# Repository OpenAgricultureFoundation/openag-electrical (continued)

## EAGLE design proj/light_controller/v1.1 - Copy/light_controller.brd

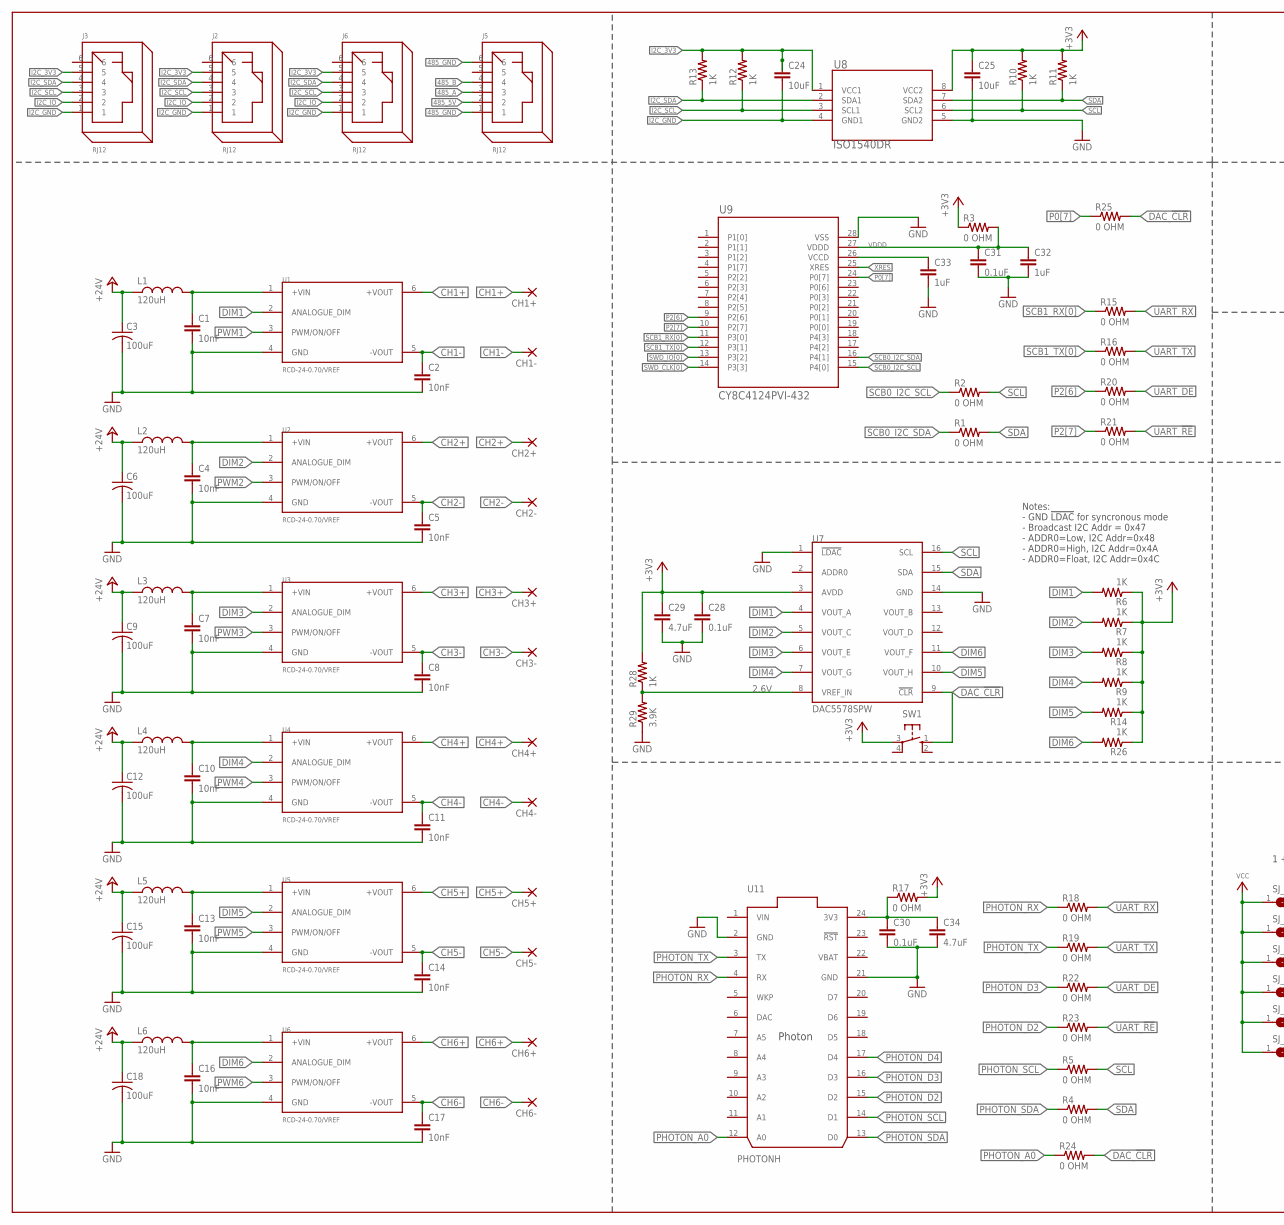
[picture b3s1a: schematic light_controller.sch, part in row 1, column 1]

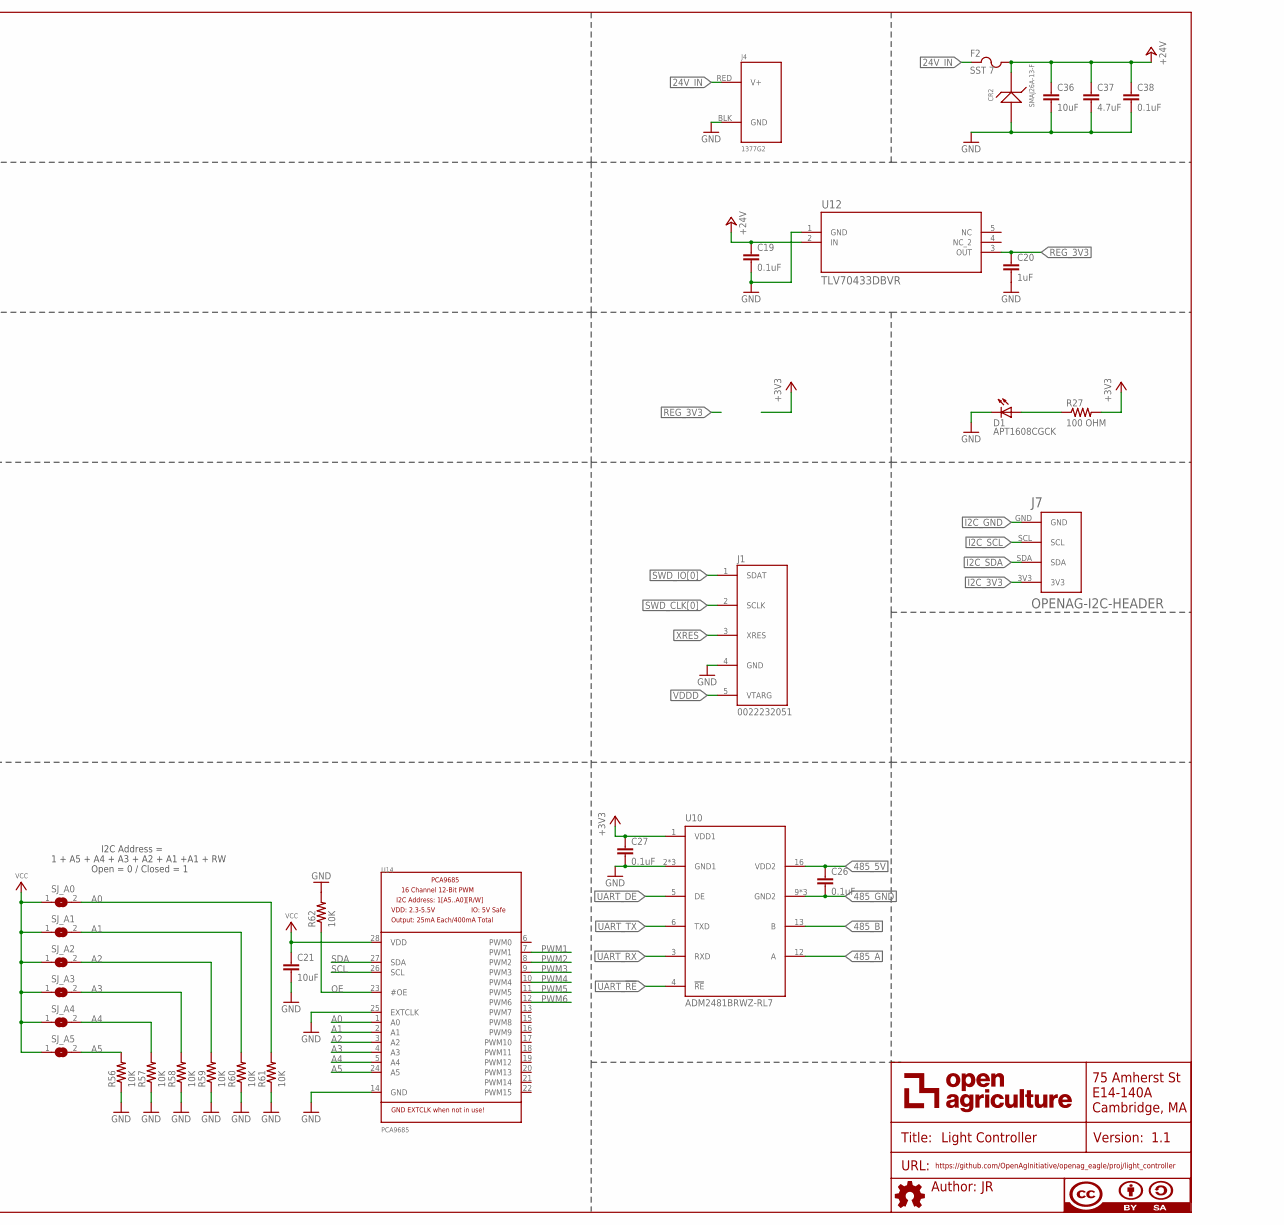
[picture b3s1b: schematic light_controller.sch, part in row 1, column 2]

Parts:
C1, C2, C4, C5, C7, C8, C10, C11, C13, C14, C16, C17: 10nF; C0603
C3, C6, C9, C12, C15, C18: 100uF; EEE-1HA101UP
C19, C26, C27, C28, C30, C31, C38: 0.1uF; C0603
C20, C32, C33: 1uF; C0603
C21, C24, C25, C36: 10uF; C0805
C29, C34, C37: 4.7uF; C0805
CH1+, CH1-, CH2+, CH2-, CH3+, CH3-, CH4+, CH4-, CH5+, CH5-, CH6+, CH6-: 3,17/1,3
CR2: SMAJ26A-13-F; SMA
D1: APT1608CGCK; CHIPLED_0603
F2: SST 7; SS
FRAME1: DOCFIELD
J1: 0022232051; 22-23-2051
J2, J3, J5, J6: RJ12
J4: 1377G2
J7: OPENAG-I2C-HEADER
L1, L2, L3, L4, L5, L6: 120uH; 74404064121
R1, R2, R3, R4, R5, R15, R16, R17, R18, R19, R20, R21, R22, R23, R24, R25: 0 OHM; RC0603N
R6, R7, R8, R9, R10, R11, R12, R13, R14, R26, R28: 1K; RC0603N
R27: 100 OHM; RC0603N
R29: 3.9K; RC0603N
R56, R57, R58, R59, R60, R61, R62: 10K; RC0603N
SJ_A0, SJ_A1, SJ_A2, SJ_A3, SJ_A4, SJ_A5: SOLDERJUMPERREFLOW_NOPASTE; SOLDERJUMPER_REFLOW_NOPASTE
SW1: BF3-1020; B3F-10XX
U1, U2, U3, U4, U5, U6: RCD-24-0.70/VREF; RCD-24-PINNED
U7: DAC5578SPW; TSSOP16
U8: ISO1540DR; D8
U9: CY8C4124PVI-432; SSOP-28
U10: ADM2481BRWZ-RL7; SOIC16LWB
U11: PHOTONH; PHOTON
U12: TLV70433DBVR; DBV5-M
U14: PCA9685; TSSOP28

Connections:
2.6V: R28.1, R29.2, U7.8 (VREF_IN)
24V_IN: F2.1, J4.RED (V+)
485_5V: C26.1, J5.2, U10.16 (VDD2)
485_A: J5.3, U10.12 (A)
485_B: J5.4, U10.13 (B)
485_GND: C26.2, J5.1, J5.6, U10.9 (GND2), U10.10 (GND2), U10.15 (GND2)
+3V3: C25.1, C27.1, C28.1, C29.1, R3.1, R6.1, R7.1, R8.1, R9.1, R10.2, R11.2, R14.1, R17.2, R26.1, R27.2, R28.2, SW1.3, U7.3 (AVDD), U8.8 (VCC2), U10.1 (VDD1)
+24V: C3.+ (1(+)), C6.+ (1(+)), C9.+ (1(+)), C12.+ (1(+)), C15.+ (1(+)), C18.+ (1(+)), C19.1, C36.1, C37.1, C38.1, CR2.1, F2.2, L1.1, L2.1, L3.1, L4.1, L5.1, L6.1, U12.2 (IN)
A0: R61.2, SJ_A0.2, U14.1 (A0)
A1: R60.2, SJ_A1.2, U14.2 (A1)
A2: R59.2, SJ_A2.2, U14.3 (A2)
A3: R58.2, SJ_A3.2, U14.4 (A3)
A4: R57.2, SJ_A4.2, U14.5 (A4)
A5: R56.2, SJ_A5.2, U14.24 (A5)
CH1+: CH1+.1, U1.6 (+VOUT)
CH1-: C2.1, CH1-.1, U1.5 (-VOUT)
CH2+: CH2+.1, U2.6 (+VOUT)
CH2-: C5.1, CH2-.1, U2.5 (-VOUT)
CH3+: CH3+.1, U3.6 (+VOUT)
CH3-: C8.1, CH3-.1, U3.5 (-VOUT)
CH4+: CH4+.1, U4.6 (+VOUT)
CH4-: C11.1, CH4-.1, U4.5 (-VOUT)
CH5+: CH5+.1, U5.6 (+VOUT)
CH5-: C14.1, CH5-.1, U5.5 (-VOUT)
CH6+: CH6+.1, U6.6 (+VOUT)
CH6-: C17.1, CH6-.1, U6.5 (-VOUT)
DAC_!CLR!: R24.2, R25.2, SW1.1 (S), U7.9 (!CLR!)
DIM1: R6.2, U1.2 (ANALOGUE_DIM), U7.4 (VOUT_A)
DIM2: R7.2, U2.2 (ANALOGUE_DIM), U7.5 (VOUT_C)
DIM3: R8.2, U3.2 (ANALOGUE_DIM), U7.6 (VOUT_E)
DIM4: R9.2, U4.2 (ANALOGUE_DIM), U7.7 (VOUT_G)
DIM5: R14.2, U5.2 (ANALOGUE_DIM), U7.10 (VOUT_H)
DIM6: R26.2, U6.2 (ANALOGUE_DIM), U7.11 (VOUT_F)
GND: C1.2, C2.2, C3.- (2(-)), C4.2, C5.2, C6.- (2(-)), C7.2, C8.2, C9.- (2(-)), C10.2, C11.2, C12.- (2(-)), C13.2, C14.2, C15.- (2(-)), C16.2, C17.2, C18.- (2(-)), C19.2, C20.2, C21.2, C25.2, C27.2, C28.2, C29.2, C30.2, C31.2, C32.2, C33.2, C34.2, C36.2, C37.2, C38.2, CR2.2, D1.C, J1.4 (GND), J4.BLK (GND), R29.1, R56.1, R57.1, R58.1, R59.1, R60.1, R61.1, R62.2, U1.4 (GND), U2.4 (GND), U3.4 (GND), U4.4 (GND), U5.4 (GND), U6.4 (GND), U7.1 (!LDAC!), U7.14 (GND), U8.5 (GND2), U9.28 (VSS), U10.2 (GND1), U10.7 (GND1), U10.8 (GND1), U11.2 (GND), U11.21 (GND), U12.1 (GND), U14.14 (GND), U14.25 (EXTCLK)
I2C_3V3: C24.1, J2.5, J3.5, J6.5, J7.3V3, R12.2, R13.2, U8.1 (VCC1)
I2C_GND: C24.2, J2.1, J3.1, J6.1, J7.GND, U8.4 (GND1)
I2C_IO: J2.2, J3.2, J6.2
I2C_SCL: J2.3, J3.3, J6.3, J7.SCL, R12.1, U8.3 (SCL1)
I2C_SDA: J2.4, J3.4, J6.4, J7.SDA, R13.1, U8.2 (SDA1)
unnamed: C1.1, L1.2, U1.1 (+VIN)
unnamed: C4.1, L2.2, U2.1 (+VIN)
unnamed: D1.A, R27.1
unnamed: C7.1, L3.2, U3.1 (+VIN)
unnamed: C10.1, L4.2, U4.1 (+VIN)
unnamed: C13.1, L5.2, U5.1 (+VIN)
unnamed: C16.1, L6.2, U6.1 (+VIN)
unnamed: C30.1, C34.1, R17.1, U11.24 (3V3)
unnamed: C33.1, U9.26 (VCCD)
OE: R62.1, U14.23 (#OE)
P0[7]: R25.1, U9.24 (P0[7])
P2[6]: R20.1, U9.9 (P2[6])
P2[7]: R21.1, U9.10 (P2[7])
PHOTON_A0: R24.1, U11.12 (A0)
PHOTON_D2: R23.1, U11.15 (D2)
PHOTON_D3: R22.1, U11.16 (D3)
PHOTON_D4: U11.17 (D4)
PHOTON_RX: R18.1, U11.4 (RX)
PHOTON_SCL: R5.1, U11.14 (D1)
PHOTON_SDA: R4.1, U11.13 (D0)
PHOTON_TX: R19.1, U11.3 (TX)
PWM1: U1.3 (PWM/ON/OFF), U14.7 (PWM1)
PWM2: U2.3 (PWM/ON/OFF), U14.8 (PWM2)
PWM3: U3.3 (PWM/ON/OFF), U14.9 (PWM3)
PWM4: U4.3 (PWM/ON/OFF), U14.10 (PWM4)
PWM5: U5.3 (PWM/ON/OFF), U14.11 (PWM5)
PWM6: U6.3 (PWM/ON/OFF), U14.12 (PWM6)
REG_3V3: C20.1, U12.3 (OUT)
SCB0_I2C_SCL: R2.1, U9.15 (P4[0])
SCB0_I2C_SDA: R1.1, U9.16 (P4[1])
SCB1_RX[0]: R15.1, U9.11 (P3[0])
SCB1_TX[0]: R16.1, U9.12 (P3[1])
SCL: R2.2, R5.2, R10.1, U7.16 (SCL), U8.6 (SCL2), U14.26 (SCL)
SDA: R1.2, R4.2, R11.1, U7.15 (SDA), U8.7 (SDA2), U14.27 (SDA)
SWD_CLK[0]: J1.2 (SCLK), U9.14 (P3[3])
SWD_IO[0]: J1.1 (SDAT), U9.13 (P3[2])
UART_!RE!: R21.2, R23.2, U10.4 (!RE!)
UART_DE: R20.2, R22.2, U10.5 (DE)
UART_RX: R15.2, R18.2, U10.3 (RXD)
UART_TX: R16.2, R19.2, U10.6 (TXD)
VBAT: U11.22 (VBAT)
VCC: C21.1, SJ_A0.1, SJ_A1.1, SJ_A2.1, SJ_A3.1, SJ_A4.1, SJ_A5.1, U14.28 (VDD)
VDDD: C31.1, C32.1, J1.5 (VTARG), R3.2, U9.27 (VDDD)
VIN: U11.1 (VIN)
XRES: J1.3 (XRES), U9.25 (XRES)

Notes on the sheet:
Notes: - GND !LDAC! for syncronous mode - Broadcast I2C Addr = 0x47 - ADDR0=Low, I2C Addr=0x48 - ADDR0=High, I2C Addr=0x4A - ADDR0=Float, I2C Addr=0x4C
1 + A5 + A4 + A3 + A2 + A1 +A1 + RW
I2C Address =
Open = 0 / Closed = 1

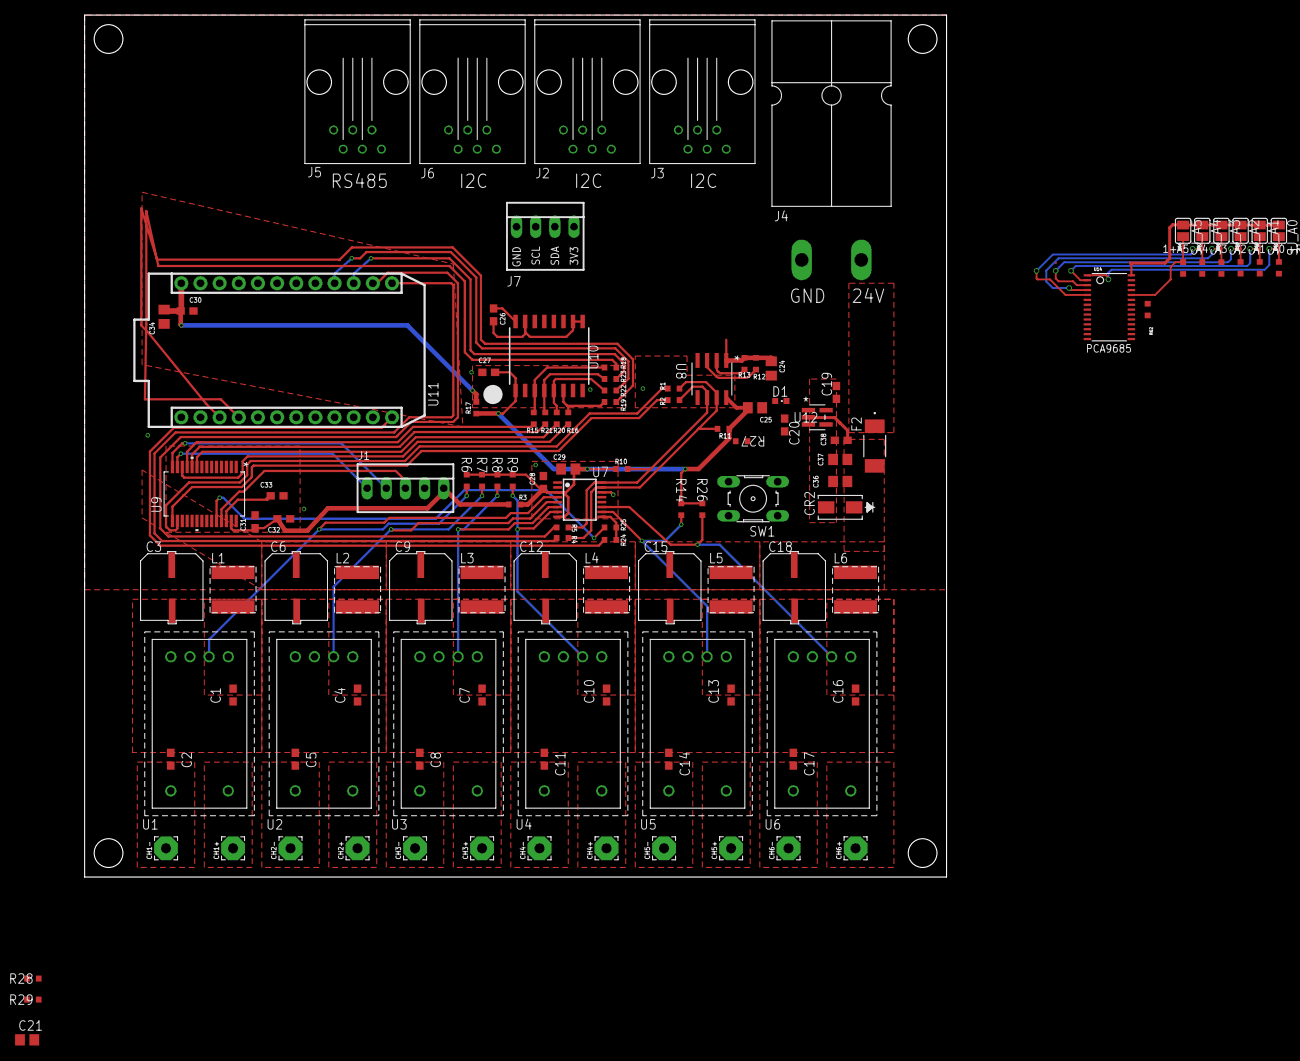
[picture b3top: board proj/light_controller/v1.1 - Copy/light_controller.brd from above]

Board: 2 copper layers, 114.3 x 114.3 mm, 120 parts (1 on the bottom side), 81 nets.

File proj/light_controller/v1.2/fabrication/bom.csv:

Qty,Value,Device,Package,Parts,Description,,
20,0 OHM,0OHM-RC0603JR-070RL,RC0603N,R1 / R2 / R3 / R4 / R5 / R15 / R16 / R17 / R18 / R19 / R20 / R21 / R22 / R23 / R24 / R25 / R30 / R31 / R32 / R33,Yageo - RC0603JR-070RL - RES SMD 0 OHM JUMPER 1/10W 0603,,
7,0.1uF,0.1UF-C0603C104K5RACTU,C0603,C19 / C26 / C27 / C28 / C30 / C31 / C38,Kemet - C0603C104K5RACTU - CAP CER 0.1UF 50V X7R 0603,,
1,0022232051,MINI-PROG3-5POS-MATING-CONNECTOR,22-23-2051,J1,Molex - 0022232051 - CONN HEADER 5POS .100 VERT TIN,,
1,100 OHM,100OHM-RC0603JR-07100RL,RC0603N,R27,Yageo - RC0603JR-07100RL - RES SMD 100 OHM 5% 1/10W 0603,,
6,100uF,100UF-EEE-1HA101UP,EEE-1HA101UP,C3 / C6 / C9 / C12 / C15 / C18,Panasonic - EEE-1HA101UP - ELECTROLYTIC CAP ALUM 100UF 20% 50V SMD,,
7,10K,10K-ERJ-3EKF1002V,RC0603N,R56 / R57 / R58 / R59 / R60 / R61 / R62,Panasonic - ERJ-3EKF1002V - RES SMD 10K OHM 1% 1/10W 0603,,
12,10nF,10NF-C0603C103K5RACTU,C0603,C1 / C2 / C4 / C5 / C7 / C8 / C10 / C11 / C13 / C14 / C16 / C17,KEMET - C0603C103K5RACTU - CAP CER 10000PF 50V X7R 0603,,
4,10uF,10UF-GMK212BBJ106KG-T,C0805,C21 / C24 / C25 / C36,Taiyo Yuden - GMK212BBJ106KG-T - CAP CER 10UF 35V X5R 0805,,
6,120uH,120UH-74404064121,74404064121,L1 / L2 / L3 / L4 / L5 / L6,Wurth Electronics - 74404064121 - FIXED IND 120UH 790MA 520 MOHM,,
1,1377G2,1377G21377G2,1377G2,J4,Anderson Powerpole - 1377G2 - RT. ANGLE 25A THRU-HOLE PCB CONTACT PAIR FOR 15/45 HOUSING,,
11,1K,1K-ERJ-PB3D1001V,RC0603N,R6 / R7 / R8 / R9 / R10 / R11 / R12 / R13 / R14 / R26 / R28,Panasonic - P20283CT-ND - RES SMD 1K OHM 0.5% 1/5W 0603,,
3,1uF,1UF-CL10A105KB8NNNC,C0603,C20 / C32 / C33,Samsung - CL10A105KB8NNNC - CAP CER 1UF 50V X5R 0603,,
1,3.9K,3.9K-RC0603JR-073K9L,RC0603N,R29,Yageo - RC0603JR-073K9L - RES SMD 3.9K OHM 5% 1/10W 0603,,
3,4.7uF,4.7UF-CL21A475KBQNNNE,C0805,C29 / C34 / C37,Samsung - CL21A475KBQNNNE - CAP CER 4.7UF 50V X5R 0805,,
4,A-2004-1-4-LP-N-R,A-2004-1-4-LP-N-R,RJ12,J2 / J3 / J5 / J6,Assmann WSW Components - A-2004-1-4-LP-N-R - RJ12 CONN MOD JACK 6P6C R/A UNSHLD,,
1,ADM2481BRWZ-RL7,ADM2481BRWZ-RL7,SOIC16LWB,U10,Analog Devices - ADM2481BRWZ-RL7 - DGTL ISO RS422/RS485 16SOIC,,
1,APT1608CGCK,APT1608CGCK,CHIPLED_0603,D1,Kingbright - APT1608CGCK - LED GREEN CLEAR 0603 SMD,,
1,BF3-1020,BF3-1020,B3F-10XX,SW1,Omron - BF3-1020 -SWITCH TACTILE SPST-NO 0.05A 24V,,
1,CY8C4124PVI-432,CY8C4124PVI-432,SSOP-28,U9,Cypress - CY8C4124PVI-432 - IC MCU 32BIT 16KB FLASH 28SSOP,,
1,DAC5578SPW,DAC5578SPW,TSSOP16,U7,Texas Instruments - DAC5578SPW,,
1,ISO1540DR,ISO1540DR,D8,U8,Texas Instruments - ISO1540DR - DGTL ISO 2.5KV 2CH I2C 8SOIC,,
1,OPENAG-I2C-HEADER,OPENAG-I2C-HEADER,OPENAG-I2C-HEADER,J7,Fits standard 100 mil header footprint,,
1,PCA9685,PCA9685PW/Q900 /118,TSSOP28,U14,NXP USA Inc. - PCA9685PW/Q900 /118 - IC LED DRVR LIN DIM 25MA 28TSSOP,,
1,PHOTONH,PHOTONHPHOTONH,PHOTON,U11,PARTICLE - PHOTONH - Tiny Wi-Fi dev board w/cloud backend,,
6,RCD-24-0.70/VREF,RCD-24-0.70/VREF,RCD-24-PINNED,U1 / U2 / U3 / U4 / U5 / U6,Recom Power - RCD-24-0.70/VREF - LED SUPPLY CC BUCK 2-35V 700MA,,
1,SMAJ26A-13-F,SMAJ26A-13-F,SMA,CR2,Diodes Incorporated - SMAJ26A-13-F - TVS DIODE 26VWM 42.1VC SMA,,
1,SST 7,SST_7,SS,F2,Bel Fuse - SST7 - FUSE BRD MNT 7A 125VAC/VDC 2SMD,,
1,TLV70433DBVR,TLV70433DBVRDBV5-M,DBV5-M,U12,Texas Instruments - TLV70433DBVR - IC REG LINEAR 3.3V 150MA SOT23-5,,

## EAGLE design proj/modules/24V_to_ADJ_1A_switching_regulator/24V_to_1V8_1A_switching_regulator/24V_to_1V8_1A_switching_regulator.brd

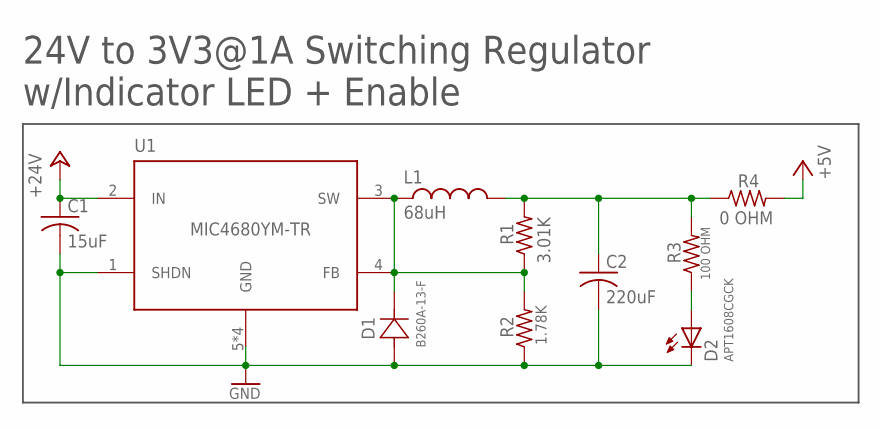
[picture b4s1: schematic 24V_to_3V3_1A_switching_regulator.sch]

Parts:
C1: 15uF; CT7343
C2: 220uF; CT7343
D1: B260A-13-F; SMA
D2: APT1608CGCK; CHIPLED_0603
L1: 68uH; UP2B
R1: 3.01K; RC0603N
R2: 1.78K; RC0603N
R3: 100 OHM; RC0603N
R4: 0 OHM; RC0603N
U1: MIC4680YM-TR; SOIC8

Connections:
+5V: R4.2
+24V: C1.+ (1(+)), U1.2 (IN)
GND: C1.- (2(-)), C2.- (2(-)), D1.2 (21), D2.C, R2.1, U1.1 (SHDN), U1.5 (GND), U1.6 (GND), U1.7 (GND), U1.8 (GND)
unnamed: D2.A, R3.1
unnamed: C2.+ (1(+)), L1.2, R1.2, R3.2, R4.1
unnamed: D1.1 (12), L1.1, R1.1, R2.2, U1.3 (SW), U1.4 (FB)

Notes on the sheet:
24V to 3V3@1A Switching Regulator w/Indicator LED + Enable

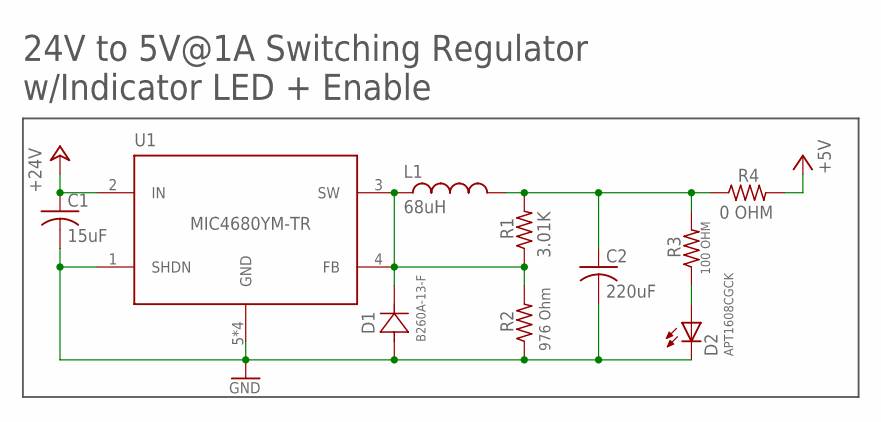
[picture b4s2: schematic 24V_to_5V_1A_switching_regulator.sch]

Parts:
C1: 15uF; CT7343
C2: 220uF; CT7343
D1: B260A-13-F; SMA
D2: APT1608CGCK; CHIPLED_0603
L1: 68uH; UP2B
R1: 3.01K; RC0603N
R2: 976 Ohm; RC0603N
R3: 100 OHM; RC0603N
R4: 0 OHM; RC0603N
U1: MIC4680YM-TR; SOIC8

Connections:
+5V: R4.2
+24V: C1.+ (1(+)), U1.2 (IN)
GND: C1.- (2(-)), C2.- (2(-)), D1.2 (21), D2.C, R2.1, U1.1 (SHDN), U1.5 (GND), U1.6 (GND), U1.7 (GND), U1.8 (GND)
unnamed: D2.A, R3.1
unnamed: C2.+ (1(+)), L1.2, R1.2, R3.2, R4.1
unnamed: D1.1 (12), L1.1, R1.1, R2.2, U1.3 (SW), U1.4 (FB)

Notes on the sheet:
24V to 5V@1A Switching Regulator w/Indicator LED + Enable

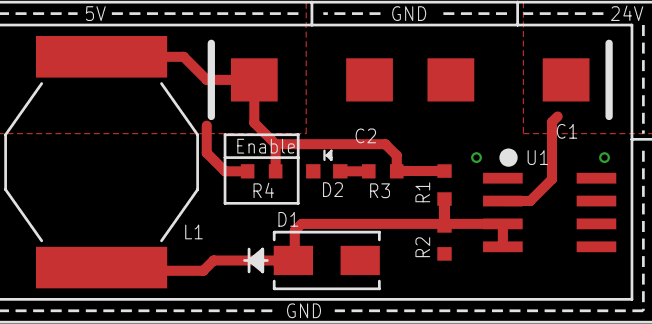
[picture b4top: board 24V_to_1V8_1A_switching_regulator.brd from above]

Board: 2 copper layers, 10 parts (0 on the bottom side), 5 nets.
